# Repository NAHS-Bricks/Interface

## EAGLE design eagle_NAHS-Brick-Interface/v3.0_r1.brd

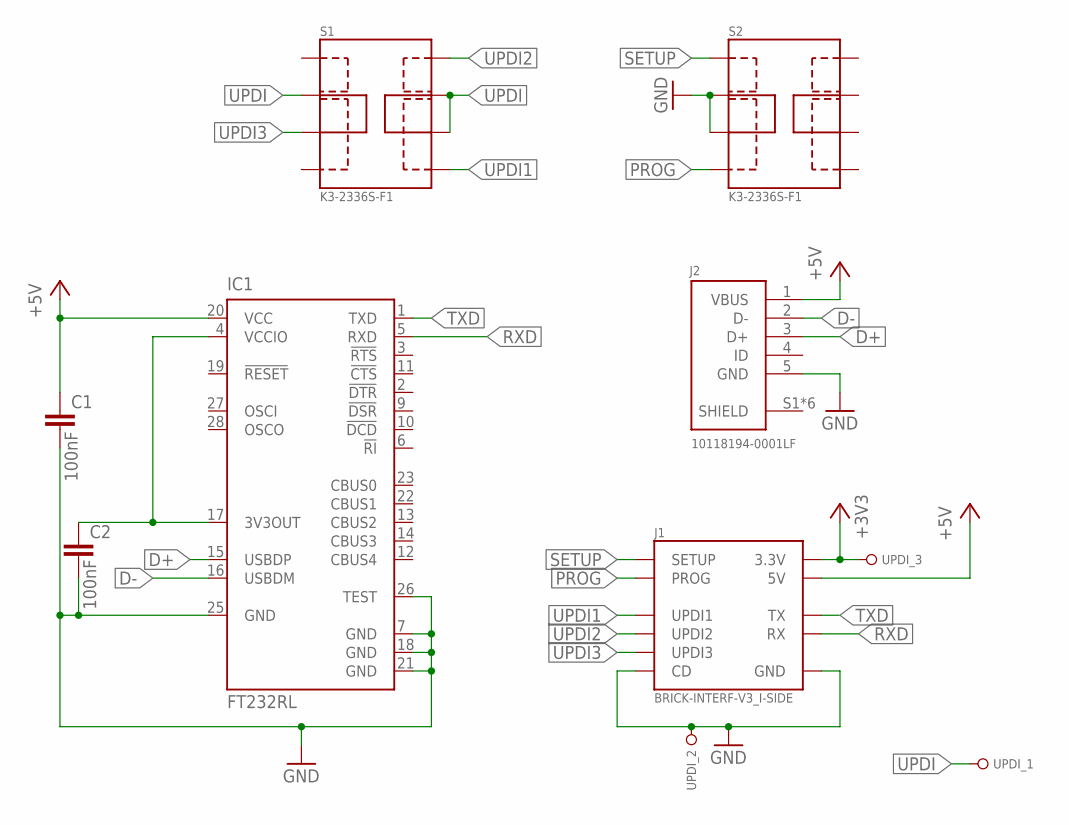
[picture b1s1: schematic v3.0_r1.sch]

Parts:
C1, C2: 100nF; C0805
IC1: FT232RL; SSOP28
J1: BRICK-INTERF-V3_I-SIDE; DF9-11S-1V(32)
J2: 10118194-0001LF
S1, S2: K3-2336S-F1
UPDI: PINHD_1X03_R_1; 1X03_R_1

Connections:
+3V3: J1.10 (3.3V), UPDI.3
+5V: C1.1, IC1.20 (VCC), J1.4 (5V), J2.1 (VBUS)
D+: IC1.15 (USBDP), J2.3 (D+)
D-: IC1.16 (USBDM), J2.2 (D-)
GND: C1.2, C2.2, IC1.7 (GND), IC1.18 (GND), IC1.21 (GND), IC1.25 (GND), IC1.26 (TEST), J1.5 (CD), J1.6 (GND), J2.5 (GND), S2.1.2, S2.1.3, UPDI.2
unnamed: C2.1, IC1.4 (VCCIO), IC1.17 (3V3OUT)
PROG: J1.3 (PROG), S2.1.4
RXD: IC1.5 (RXD), J1.1 (RX)
SETUP: J1.2 (SETUP), S2.1.1
SHIELD: J2.S1 (SHIELD), J2.S2 (SHIELD), J2.S3 (SHIELD), J2.S4 (SHIELD), J2.S5 (SHIELD), J2.S6 (SHIELD)
TXD: IC1.1 (TXD), J1.11 (TX)
UPDI: S1.1.2, S1.2.2, S1.2.3, UPDI.1
UPDI1: J1.7 (UPDI1), S1.2.4
UPDI2: J1.8 (UPDI2), S1.2.1
UPDI3: J1.9 (UPDI3), S1.1.3

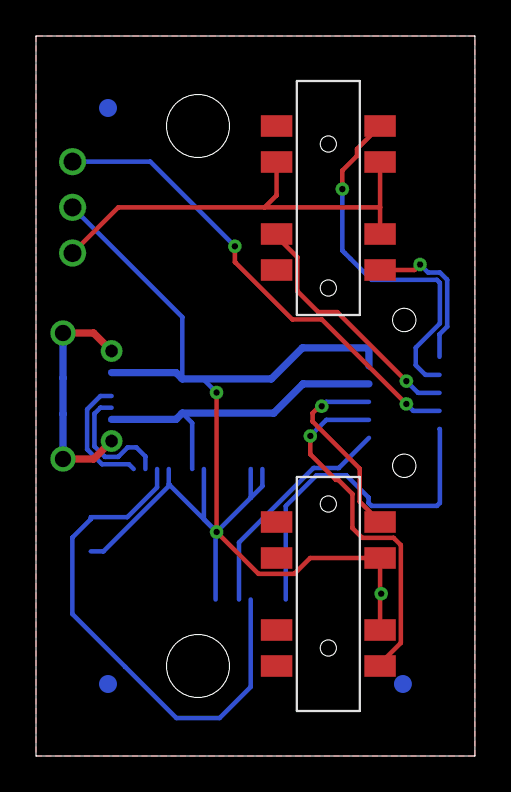
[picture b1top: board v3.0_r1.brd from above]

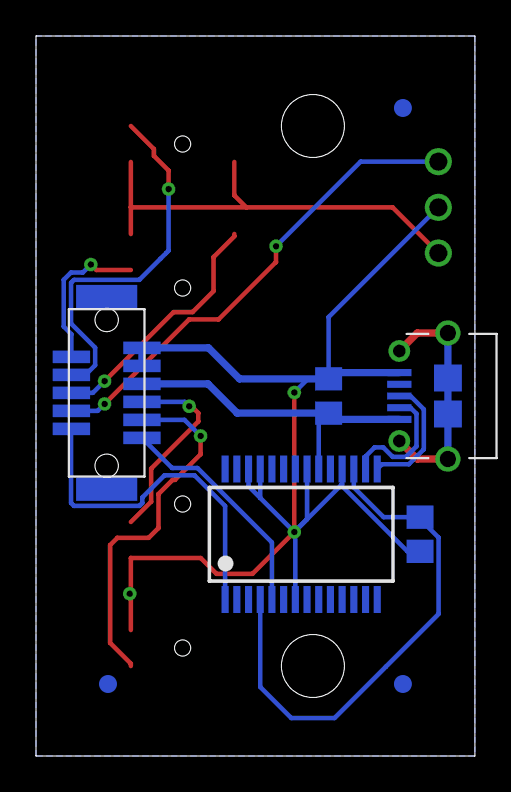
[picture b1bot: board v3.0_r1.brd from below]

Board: 2 copper layers, 24.4 x 40.0 mm, 11 parts (8 on the bottom side), 15 nets.

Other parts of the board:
U$1, U$2, U$3: FIDUCIAL

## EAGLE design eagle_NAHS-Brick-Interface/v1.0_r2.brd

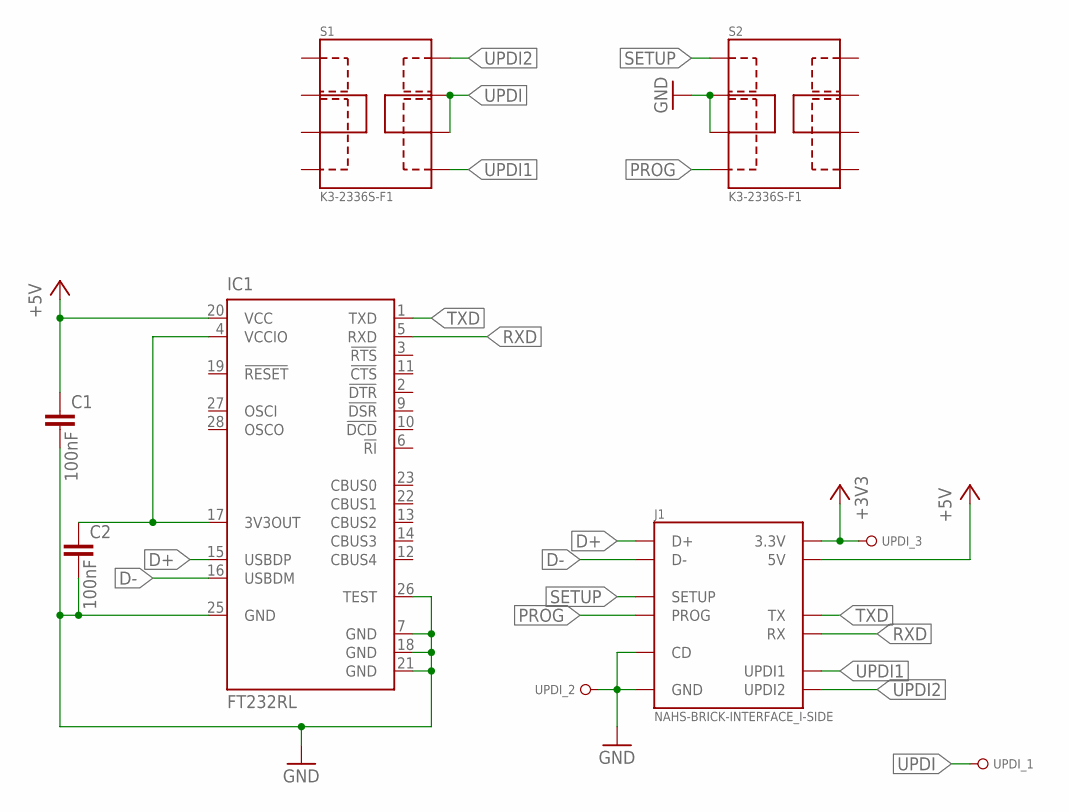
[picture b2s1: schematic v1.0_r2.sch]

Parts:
C1, C2: 100nF; C0805
IC1: FT232RL; SSOP28
J1: NAHS-BRICK-INTERFACE_I-SIDE; 54102-0164
S1, S2: K3-2336S-F1
UPDI: PINHD_1X03_R_1; 1X03_R_1

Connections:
+3V3: J1.16 (3.3V), UPDI.3
+5V: C1.1, IC1.20 (VCC), J1.5 (5V), J1.6 (5V)
D+: IC1.15 (USBDP), J1.9 (D+)
D-: IC1.16 (USBDM), J1.10 (D-)
GND: C1.2, C2.2, IC1.7 (GND), IC1.18 (GND), IC1.21 (GND), IC1.25 (GND), IC1.26 (TEST), J1.11 (GND), J1.12 (GND), J1.13 (CD), S2.1.2, S2.1.3, UPDI.2
unnamed: C2.1, IC1.4 (VCCIO), IC1.17 (3V3OUT)
PROG: J1.1 (PROG), S2.1.4
RXD: IC1.5 (RXD), J1.8 (RX)
SETUP: J1.2 (SETUP), S2.1.1
TXD: IC1.1 (TXD), J1.7 (TX)
UPDI: S1.2.2, S1.2.3, UPDI.1
UPDI1: J1.15 (UPDI1), S1.2.4
UPDI2: J1.14 (UPDI2), S1.2.1

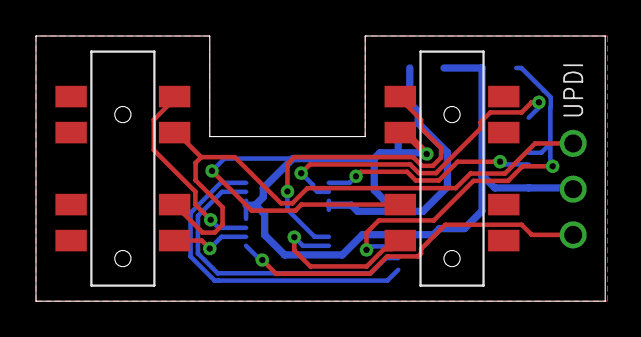
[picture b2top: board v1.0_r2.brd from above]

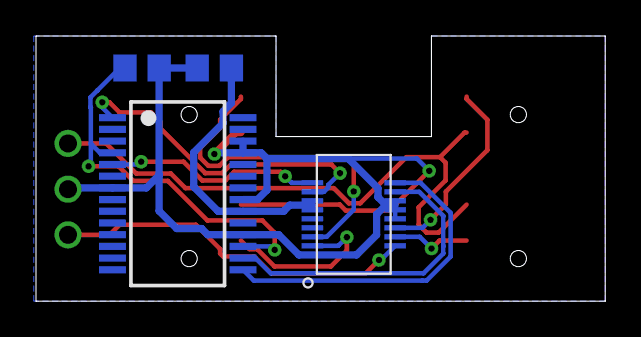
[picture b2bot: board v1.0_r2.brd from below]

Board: 2 copper layers, 31.6 x 14.7 mm, 7 parts (4 on the bottom side), 13 nets.

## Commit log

2021-01-14 basic design and routing done
2021-01-16 routing done
2021-01-17 added planes
2021-01-19 Finale Version v1.0_r1 die an JLCPCB übermittelt wurde
2021-02-18 v1.0 R2 board vorbereitet
2021-05-08 v2.0_r1 Board Design
2021-05-11 added third UPDI Pin
2021-05-14 cleaned version of brick interface
2021-07-22 board v3.0 r1 designed
2021-10-04 board v3.0 r2 designed
2022-09-11 v4.0 r1 should be done
2023-11-16 v4.0 r1 Board done
2023-11-16 added LICENSE
2023-11-16 added zip files to be ignored
2023-11-21 v4.0 r2 Board done
2023-11-22 v4.0 r2 ibom done
2023-12-03 changed colors of LEDs
2024-02-22 v4.0 r3 Board started - had swapped pins on UPDI header
